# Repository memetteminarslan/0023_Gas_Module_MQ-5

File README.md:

# 0023_Gas_Module_MQ-5

You are seeing a large number of widely used MQ-5 in electronic development kits. More information coming soon...

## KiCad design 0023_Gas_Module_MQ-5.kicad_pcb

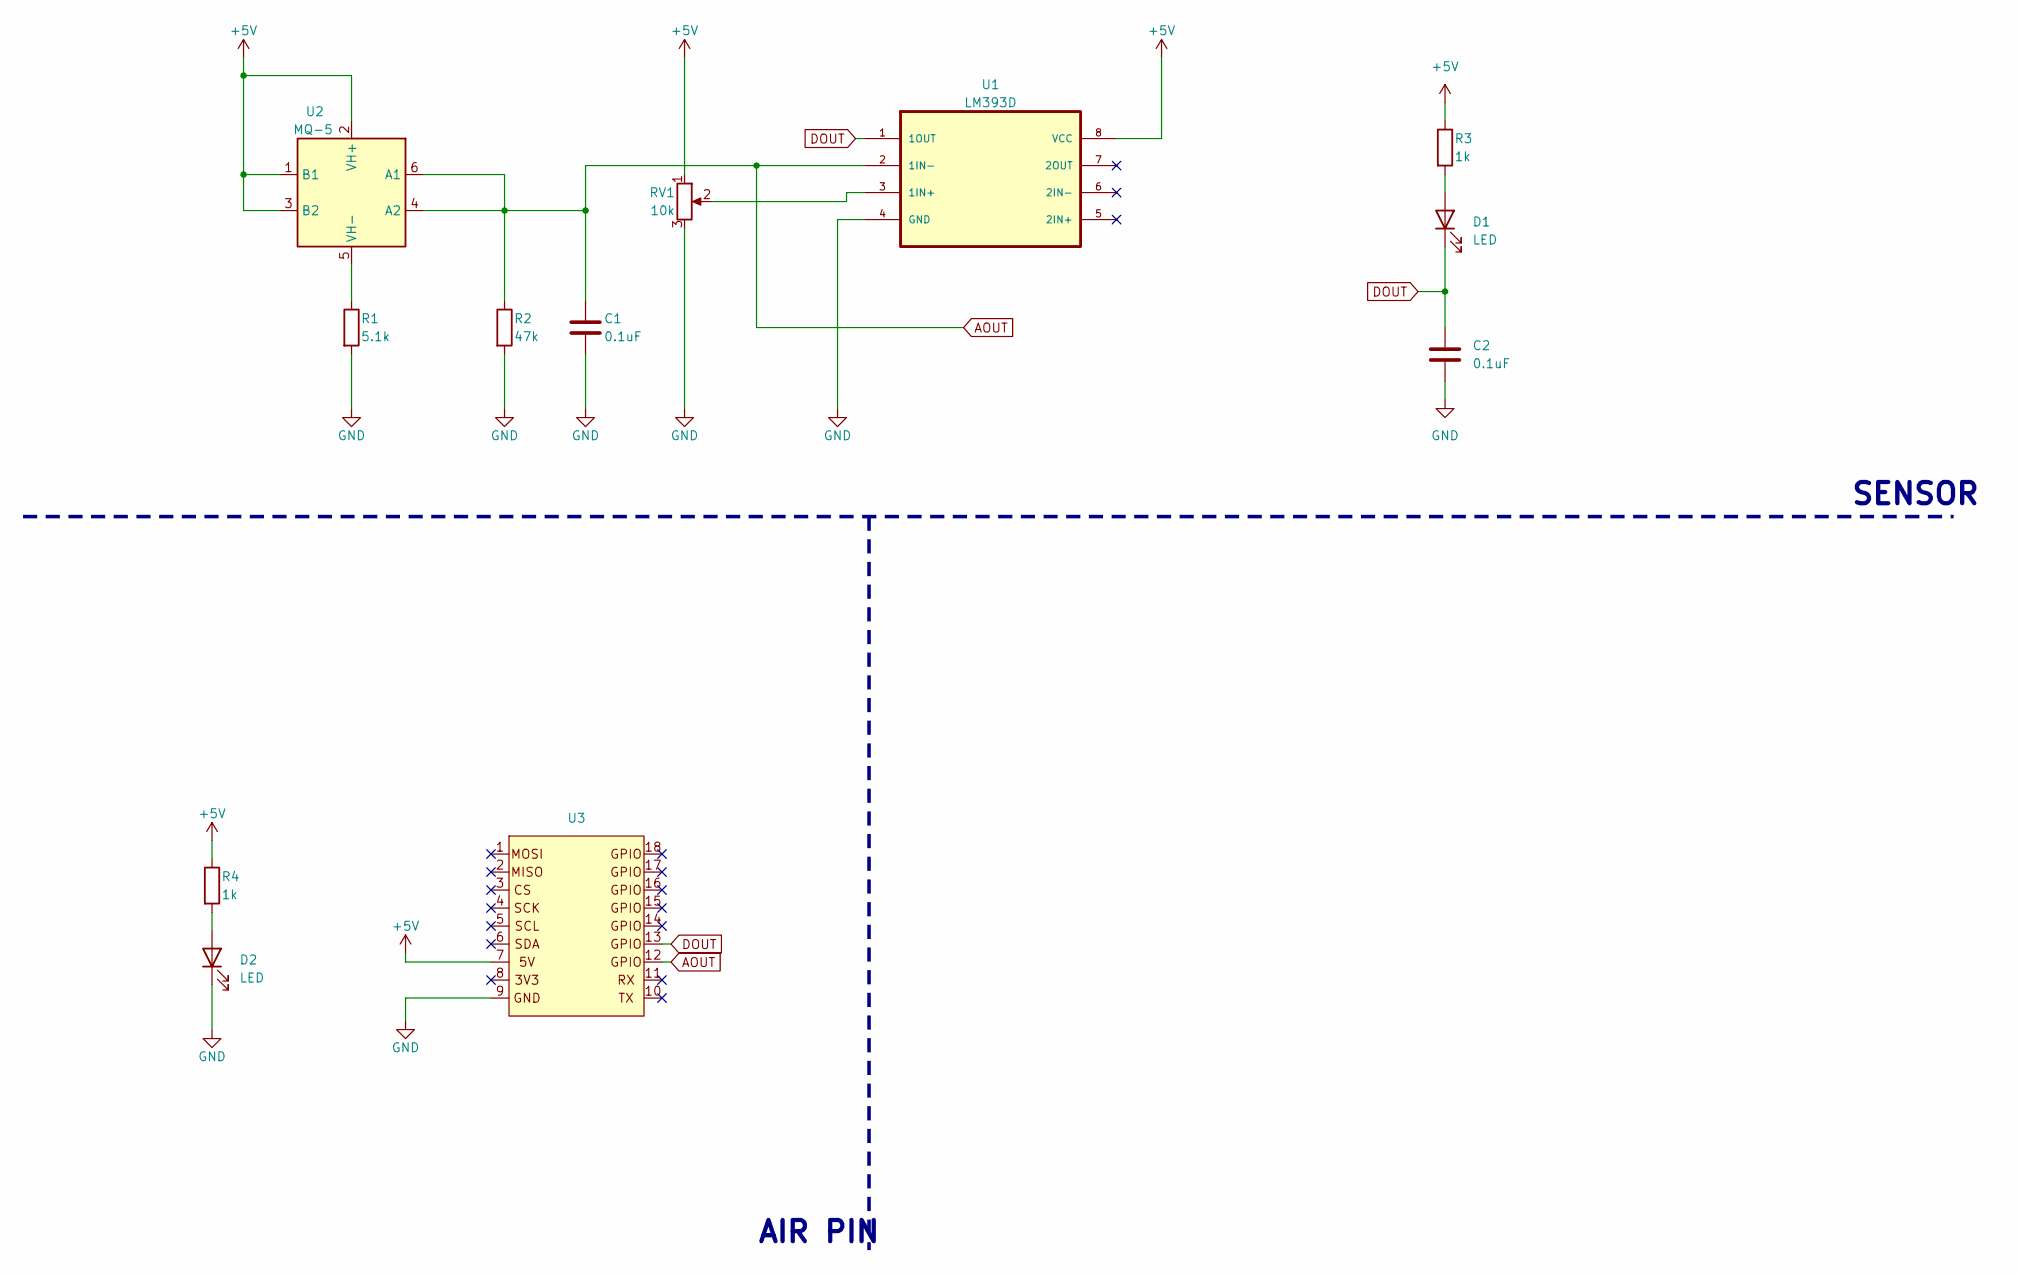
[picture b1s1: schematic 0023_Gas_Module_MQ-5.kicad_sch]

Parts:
C1, C2: 0.1uF; C_0805_2012Metric
D1, D2: LED; LED_0805_2012Metric
R1: 5.1k; R_0805_2012Metric
R2: 47k; R_0805_2012Metric
R3, R4: 1k; R_0805_2012Metric
RV1: 10k; 3362P_1
U1: LM393D; SOIC127P599X175-8N
U2: MQ-5; MQ-6
U3: pin_header

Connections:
+5V: R3.1, R4.1, RV1.1, U1.8 (VCC), U2.1 (B1), U2.2 (VH+), U2.3 (B2), U3.7
AOUT: C1.1, R2.1, U1.2 (1IN-), U2.4 (A2), U2.6 (A1), U3.12
DOUT: C2.1, D1.1 (K), U1.1 (1OUT), U3.13
GND: C1.2, C2.2, D2.1 (K), R1.2, R2.2, RV1.3, U1.4 (GND), U3.9
unnamed: D1.2 (A), R3.2
unnamed: D2.2 (A), R4.2
unnamed: RV1.2, U1.3 (1IN+)
unnamed: R1.1, U2.5 (VH-)

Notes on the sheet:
SENSOR
AIR PIN

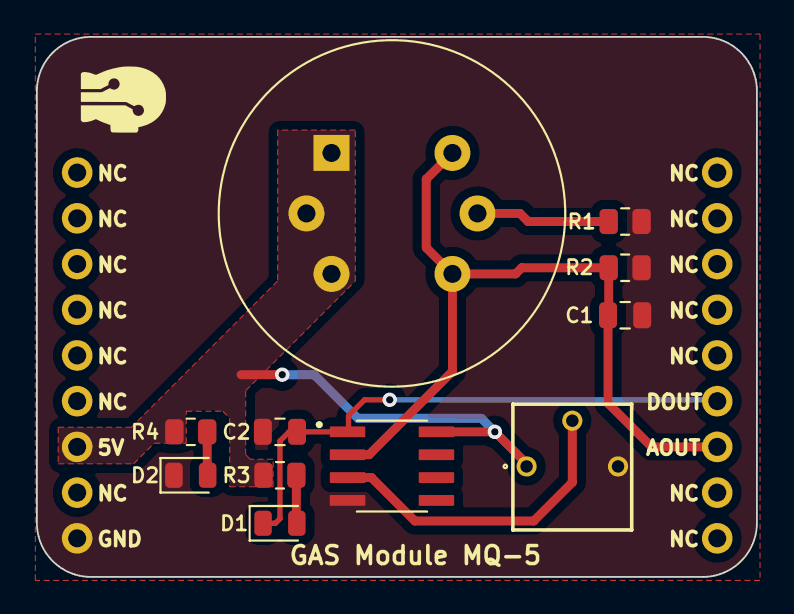
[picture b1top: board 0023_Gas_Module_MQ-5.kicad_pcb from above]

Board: 2 copper layers, 40.0 x 30.0 mm, 12 parts (0 on the bottom side), 8 nets.
